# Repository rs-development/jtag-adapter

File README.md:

# jtag-adapter
JTAG Adapter PCB

Work still in process, PCB is not tested yet

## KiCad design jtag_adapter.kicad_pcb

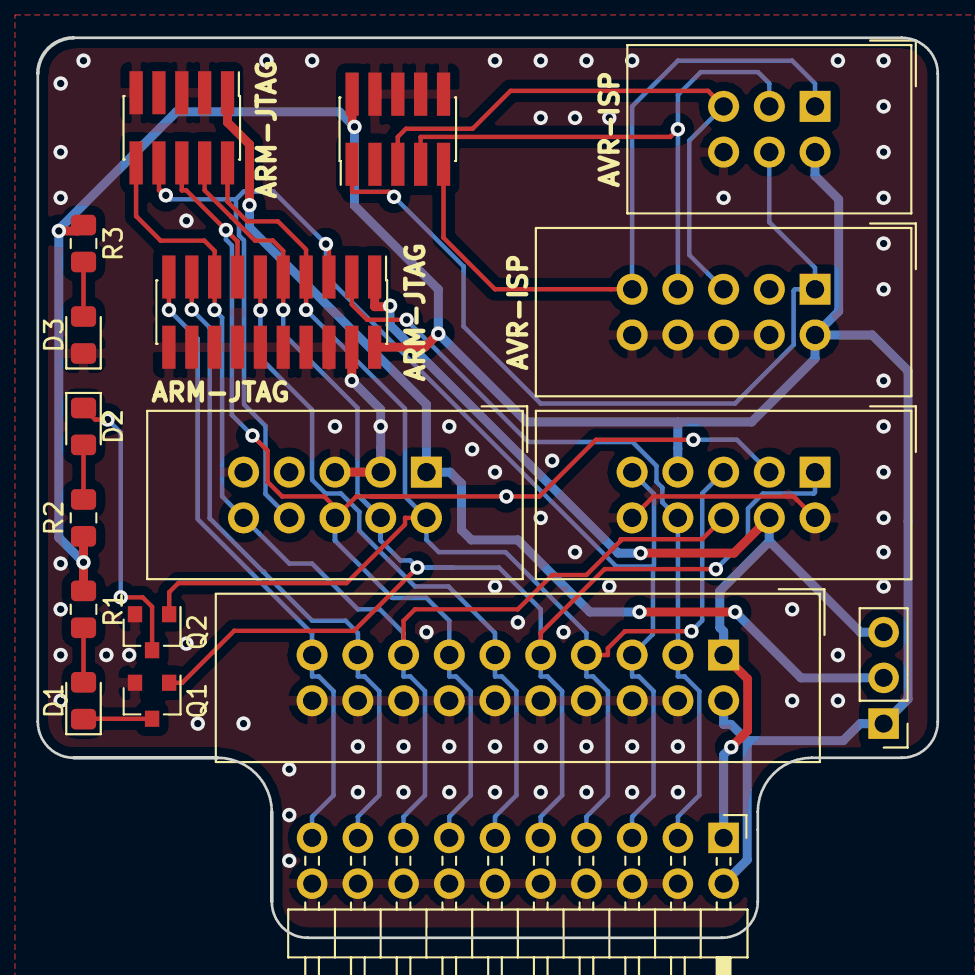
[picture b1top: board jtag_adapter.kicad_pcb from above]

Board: 2 copper layers, 50.0 x 50.0 mm, 18 parts (0 on the bottom side), 22 nets.

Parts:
D1, D2, D3: LED; LED_0805_2012Metric_Pad1.15x1.40mm_HandSolder
J1: Conn_ARM_JTAG_SWD_10; PinHeader_2x05_P1.27mm_Vertical_SMD
J2: Conn_ARM_JTAG_SWD_20; PinHeader_2x10_P2.54mm_Horizontal
J3: Conn_ARM_JTAG_SWD_10; IDC-Header_2x05_P2.54mm_Vertical
J4: Conn_ARM_JTAG_SWD_20; PinHeader_2x10_P1.27mm_Vertical_SMD
J5: Conn_ARM_JTAG_SWD_20; IDC-Header_2x10_P2.54mm_Vertical
J6: AVR-JTAG-10; IDC-Header_2x05_P2.54mm_Vertical
J7: AVR-ISP-6; IDC-Header_2x03_P2.54mm_Vertical
J8: AVR-ISP-10; IDC-Header_2x05_P2.54mm_Vertical
J9: AVR-ISP-10; PinHeader_2x05_P1.27mm_Vertical_SMD
JP1: Jumper_3_Bridged12; PinHeader_1x03_P2.54mm_Vertical
Q1, Q2: BSS138; SOT-23
R1, R2, R3: 330; R_0805_2012Metric_Pad1.15x1.40mm_HandSolder

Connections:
/DBGACK: J2.19, J4.19, J5.19
/DBGRQ: J2.17, J4.17, J5.17
/MISO: J7.1, J8.9, J9.9
/MOSI: J7.4, J8.1, J9.1
/RST: J7.5, J8.5, J9.5
/RTCK: J2.11, J4.11, J5.11
/SCK: J7.3, J8.7, J9.7
/SRST: J1.10, J2.15, J3.10, J4.15, J5.15, J6.6
/TCK-SWDCLK: J1.4, J2.9, J3.4, J4.9, J5.9, J6.1, Q1.1
/TDI: J1.8, J2.5, J3.8, J4.5, J5.5, J6.9
/TDO-SWO: J1.6, J2.13, J3.6, J4.13, J5.13, J6.3
/TMS-SWDIO: J1.2, J2.7, J3.2, J4.7, J5.7, J6.5, Q2.1
/TRST: J2.3, J4.3, J5.3, J6.8
/VCC_SELECT: J1.1, J3.1, JP1.2
/VTREF: J2.1, J4.1, J5.1, J6.4, JP1.3
GND: D3.1, J1.3, J1.5, J1.9, J2.4, J2.6, J2.8, J2.10, J2.12, J2.14, J2.16, J2.18, J2.20, J3.3, J3.5, J3.9, J4.4, J4.6, J4.8, J4.10, J4.12, J4.14, J4.16, J4.18, J4.20, J5.4, J5.6, J5.8, J5.10, J5.12, J5.14, J5.16, J5.18, J5.20, J6.2, J6.10, J7.6, J8.4, J8.6, J8.8, J8.10, J9.4, J9.6, J9.8, J9.10, Q1.2, Q2.2
unnamed: D1.1, Q1.3
unnamed: D1.2, R1.2
unnamed: D2.1, Q2.3
unnamed: D2.2, R2.2
unnamed: D3.2, R3.2
VCC: J2.2, J4.2, J5.2, J6.7, J7.2, J8.2, J9.2, JP1.1, R1.1, R2.1, R3.1

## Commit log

2018-11-23 Update issue templates
2018-11-23 small schematic fix and created silkscreen printings
2018-12-21 finished pcb and created fabrication data
